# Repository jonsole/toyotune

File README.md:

# toyotune

Reverse engineering and ROM tuning for Toyota ECUs built on the Toshiba/Denso
8X (D8X) microcontroller — a proprietary part with an instruction set derived
from the Motorola 68HC11.

The best entry point is
**[Inside the 3S-GTE ECU](roms/3S-GTE/gen3/ecu_overview.md)**, an
architectural tour of the 1993 SW20 MR2 turbo ECU: three processors, adaptive
fuel trim and per-cylinder knock learning in 16 KB of ROM.

## What's here

- **[`roms/`](roms/)** — disassembly, annotation and tuned-ROM production.
  One directory per engine family (1G-GTE, 1G-GZE, 1JZ-GTE, 1UZ-FE, 3S-GE,
  3S-GTE, 3VZ-FE, 4A-GE), each holding one subdirectory per ECU part number.
  - [`roms/3S-GTE/`](roms/3S-GTE/) is the most thoroughly documented family —
    its [README](roms/3S-GTE/README.md) maps every part number to market,
    vehicle and CPU, and [`gen3/`](roms/3S-GTE/gen3/) holds the subsystem
    write-ups.
  - [`roms/docs/`](roms/docs/) documents the D8X MCU itself — instruction
    set, opcode matrix, registers — which every family here shares.
  - [`roms/d8x_assembler/`](roms/d8x_assembler/) is a Python reimplementation
    of the D8X assembler, and what the Makefiles actually build with.
- **[`hw/`](hw/)** — the Toyotune interface board: PCB, CPLD and host-MCU
  firmware for reading and rewriting these ECUs, including live access while
  the engine is running.
- **`sw/`** — IDA Pro installs used to open the `.idb` databases.

## Status

Ongoing and incomplete. The 3S-GTE Gen 3 pair is the furthest along; other
families are largely raw disassembly. Coverage is stated honestly in each
document — see
[session_journal.md](roms/3S-GTE/gen3/session_journal.md) for what is done
and what is pending.

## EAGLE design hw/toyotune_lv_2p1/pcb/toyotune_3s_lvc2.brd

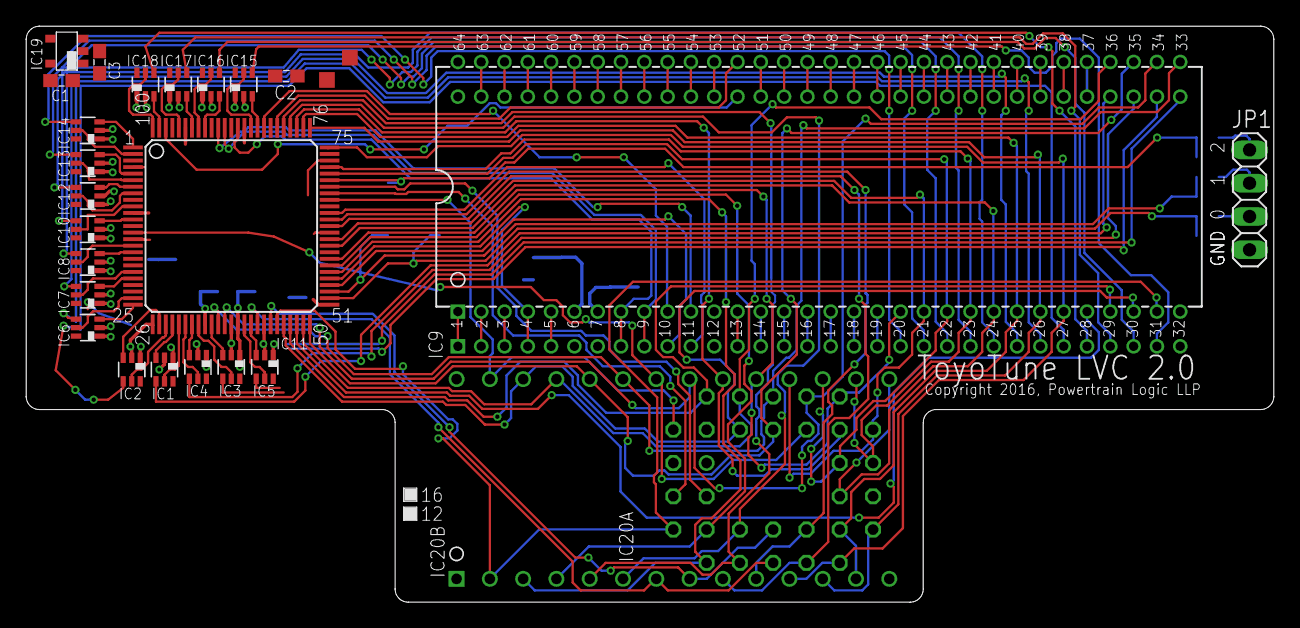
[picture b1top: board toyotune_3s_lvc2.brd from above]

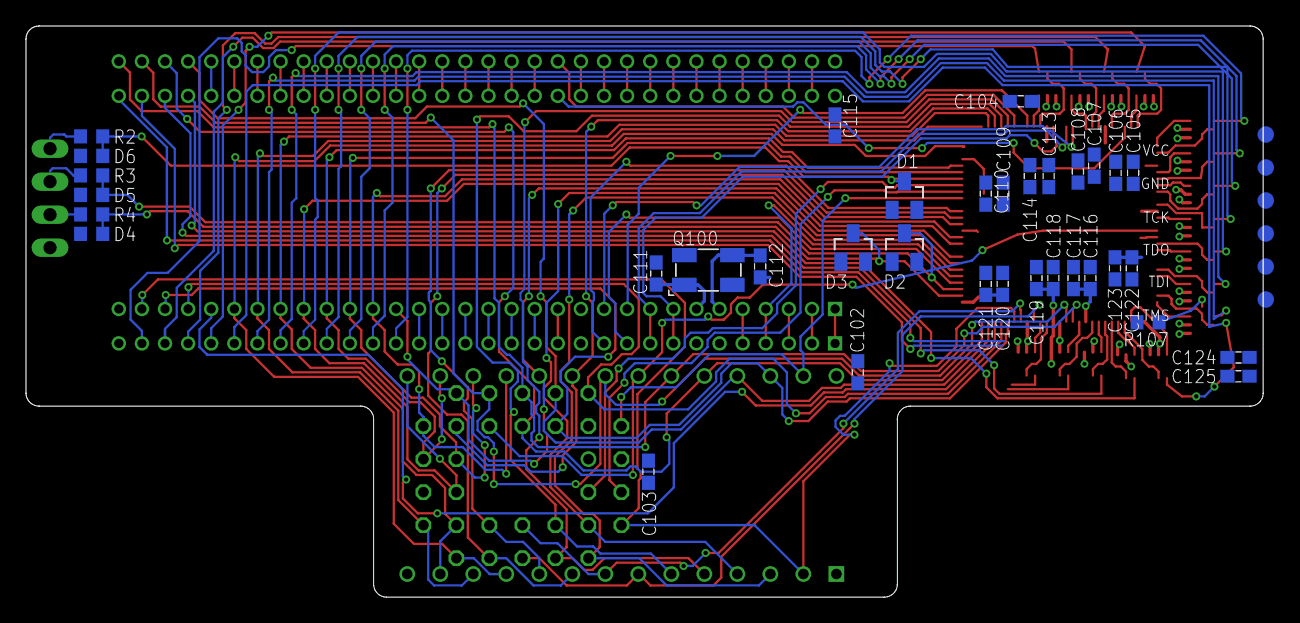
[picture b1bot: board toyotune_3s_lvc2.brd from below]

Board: 2 copper layers, 95.2 x 44.0 mm, 64 parts (36 on the bottom side), 138 nets.

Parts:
C1, C3: 1uF; C0603
C2, C102, C103, C104, C105, C107, C110, C114, C115, C116, C119, C120, C123, C124, C125: 0.1uF; C0603
C106, C108, C109, C113, C117, C118, C121, C122: 0.01uF; C0603
C111, C112: 10pF; C0603
D1, D2, D3: BAT54S; SOT23
D4, D5, D6: PGB1010603; R0603
IC1, IC2, IC3, IC4, IC5, IC6, IC7, IC8, IC10, IC12, IC13, IC15, IC16, IC17, IC18: SN74LVC1T45DCK; DCK_R-PDSO-G6
IC9: D15180X-XXXX; SDIP-64
IC11: XCR3128XL; VQ100
IC14: SN74LVC1T45; DCK_R-PDSO-G6
IC19: TLV70033; DDC_R-PDSO-G5
IC20A: SST39SF020WH; S32
IC20B: AT29C256; PDIP28
JP1: 1X04
JP100: JTAG; 1X06_SMD
Q100: 16Mhz; CRYSTAL-SMD-5X3
R2, R3, R4: 470R; R0603
R107: 10K; R0603
TP_GND: TPSQTP12SQ; TP12SQ
TP_VCC: TPSQTP12SQ; TP12SQ
U1: D151803-CONN; SDIP-64-CONN

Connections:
!D_HALT: IC9.51, U1.51
!D_INIT: IC9.52, IC11.81
!D_IRL: IC9.5, U1.5
!D_IRP: IC9.4, IC11.55, U1.4
!D_NMI: IC9.3, U1.3
!D_RD: IC9.10, IC11.83
!D_TEST: IC9.49, U1.49
!D_WDC: IC9.53, U1.53
!D_WI: IC9.50, U1.50
!D_WR: IC9.11, IC11.89
!E_INIT: IC11.98, U1.52
!E_IS: IC11.54, U1.10
!E_OS: IC11.65, U1.11
!M_RD: IC11.14, IC20A.24, IC20B.22
!M_ROM_CS: IC11.78, IC20A.22, IC20B.20
C_DRA0: IC1.5, IC11.30
C_DRA1: IC4.5, IC11.31
C_DRA2: IC3.5, IC11.33
C_DRA3: IC5.5, IC11.40
C_DRA4: IC11.85, IC15.5
C_DRA5: IC11.93, IC16.5
C_DRA6: IC11.96, IC17.5
C_DRA7: IC11.100, IC18.5
C_DRB0: IC2.5, IC11.28
C_DRB1: IC6.5, IC11.24
C_DRB2: IC7.5, IC11.20
C_DRB3: IC8.5, IC11.16
C_DRB4: IC10.5, IC11.10
C_DRB5: IC11.8, IC12.5
C_DRB6: IC11.6, IC13.5
C_DRB7: IC11.2, IC14.5
C_PA0: IC1.3, IC11.29
C_PA1: IC4.3, IC11.32
C_PA2: IC3.3, IC11.35
C_PA3: IC5.3, IC11.41
C_PA4: IC11.84, IC15.3
C_PA5: IC11.92, IC16.3
C_PA6: IC11.94, IC17.3
C_PA7: IC11.99, IC18.3
C_PB0: IC2.3, IC11.27
C_PB1: IC6.3, IC11.25
C_PB2: IC7.3, IC11.21
C_PB3: IC8.3, IC11.17
C_PB4: IC10.3, IC11.12
C_PB5: IC11.7, IC12.3
C_PB6: IC11.5, IC13.3
C_PB7: IC11.1, IC14.3
D1_XIN: C112.2, IC9.6, Q100.3
D1_XOUT: C111.1, IC9.7, Q100.1
D_A8: IC9.36, IC11.49, IC20A.27, IC20B.25
D_A9: IC9.35, IC11.50, IC20A.26, IC20B.24
D_A10: IC9.34, IC11.37, IC20A.23, IC20B.21
D_A11: IC9.33, IC11.36, IC20A.25, IC20B.23
D_A12: IC9.31, IC11.45, IC20A.4, IC20B.2
D_A13: IC9.30, IC11.46, IC20A.28, IC20B.26
D_A14: IC9.29, IC11.47, IC20A.29
D_A15: IC9.28, IC11.48
D_ADR: IC9.9, IC11.90, U1.9
D_AL0: IC11.64, IC20A.12, IC20B.10
D_AL1: IC11.63, IC20A.11, IC20B.9
D_AL2: IC11.44, IC20A.10, IC20B.8
D_AL3: IC11.42, IC20A.9, IC20B.7
D_AL4: IC11.79, IC20A.8, IC20B.6
D_AL5: IC11.80, IC20A.7, IC20B.5
D_AL6: IC11.57, IC20A.6, IC20B.4
D_AL7: IC11.56, IC20A.5, IC20B.3
D_ASR0: IC9.2, U1.2
D_ASR1: IC9.1, U1.1
D_ASR2: IC9.63, U1.63
D_ASR3: IC9.62, U1.62
D_CCLK: IC9.8, IC11.87, U1.8
D_DA0: IC9.27, IC11.75, IC20A.13, IC20B.11
D_DA1: IC9.26, IC11.76, IC20A.14, IC20B.12
D_DA2: IC9.25, IC11.77, IC20A.15, IC20B.13
D_DA3: IC9.24, IC11.60, IC20A.17, IC20B.15
D_DA4: IC9.23, IC11.72, IC20A.18, IC20B.16
D_DA5: IC9.22, IC11.71, IC20A.19, IC20B.17
D_DA6: IC9.21, IC11.61, IC20A.20, IC20B.18
D_DA7: IC9.20, IC11.58, IC20A.21, IC20B.19
D_DOUT0: IC9.61, U1.61
D_DOUT1: IC9.60, U1.60
D_DOUT2: IC9.59, U1.59
D_DOUT3: IC9.58, U1.58
D_DOUT4: IC9.57, U1.57
D_DOUT5: IC9.56, U1.56
D_DOUT6: IC9.55, U1.55
D_DOUT7: IC9.54, U1.54
D_PA0: IC1.4, U1.36
D_PA1: IC4.4, U1.35
D_PA2: IC3.4, U1.34
D_PA3: IC5.4, U1.33
D_PA4: IC15.4, U1.31
D_PA5: IC16.4, U1.30
D_PA6: IC17.4, U1.29
D_PA7: IC18.4, U1.28
D_PB0: IC2.4, U1.27
D_PB1: IC6.4, U1.26
D_PB2: IC7.4, U1.25
D_PB3: IC8.4, U1.24
D_PB4: IC10.4, U1.23
D_PB5: IC12.4, U1.22
D_PB6: IC13.4, U1.21
D_PB7: IC14.4, U1.20
D_PC0: IC9.48, U1.48
D_PC1: IC9.47, U1.47
D_PC2: IC9.46, U1.46
D_PC3: IC9.45, U1.45
D_PC4: IC9.44, U1.44
D_PC5: IC9.43, U1.43
D_PC6: IC9.42, U1.42
D_PC7: IC9.41, U1.41
D_PD0: IC9.40, U1.40
D_PD1: IC9.39, U1.39
D_PD2: IC9.38, U1.38
D_PD3: IC9.37, U1.37
D_SCLK: IC9.13, U1.13
D_SIN0: IC9.17, U1.17
D_SIN1: IC9.16, U1.16
D_SIN2: IC9.15, U1.15
D_SIN3: IC9.14, U1.14
D_SOUT0: IC9.19, U1.19
D_SOUT1: IC9.18, U1.18
GND: C1.2, C2.1, C3.2, C102.1, C103.1, C104.1, C105.1, C106.1, C107.1, C108.1, C109.1, C110.1, C111.2, C112.1, C113.1, C114.1, C115.1, C116.1, C117.1, C118.1, C119.1, C120.1, C121.1, C122.1, C123.1, C124.1, C125.1, D1.1, D2.1, D3.1, D4.1, D5.1, D6.1, IC1.2, IC2.2, IC3.2, IC4.2, IC5.2, IC6.2, IC7.2, IC8.2, IC9.12, IC9.32, IC10.2, IC11.11, IC11.26, IC11.38, IC11.43, IC11.59, IC11.74, IC11.86, IC11.95, IC12.2, IC13.2, IC14.2, IC15.2, IC16.2, IC17.2, IC18.2, IC19.2, IC20A.1, IC20A.16, IC20B.14, JP1.1, JP100.GND, TP_GND.TP, U1.32
MSEL0: D3.3, D4.2, IC11.52, R4.1
MSEL0_ECU: JP1.2, R4.2
MSEL1: D2.3, D5.2, IC11.53, R3.1
MSEL1_ECU: JP1.3, R3.2
MSEL2: D1.3, D6.2, IC11.70, R2.1
MSEL2_ECU: JP1.4, R2.2
M_A15: IC11.69, IC20A.3
M_A16: IC11.68, IC20A.2
M_A17/M_A14: IC11.67, IC20A.30, IC20B.27
TCK: IC11.62, JP100.TCK
TDI: IC11.4, JP100.TDI
TDO: IC11.73, JP100.TDO
TMS: IC11.15, JP100.TMS, R107.1
VCC: C2.2, C3.1, C102.2, C103.2, C115.2, C124.2, IC1.6, IC2.6, IC3.6, IC4.6, IC5.6, IC6.6, IC7.6, IC8.6, IC9.64, IC10.6, IC12.6, IC13.6, IC14.6, IC15.6, IC16.6, IC17.6, IC18.6, IC19.1, IC19.3, IC20A.31, IC20A.32, IC20B.1, IC20B.28, TP_VCC.TP, U1.64
VCC_CPLD: C1.1, C104.2, C105.2, C106.2, C107.2, C108.2, C109.2, C110.2, C113.2, C114.2, C116.2, C117.2, C118.2, C119.2, C120.2, C121.2, C122.2, C123.2, C125.2, D1.2, D2.2, D3.2, IC1.1, IC2.1, IC3.1, IC4.1, IC5.1, IC6.1, IC7.1, IC8.1, IC10.1, IC11.3, IC11.18, IC11.34, IC11.39, IC11.51, IC11.66, IC11.82, IC11.91, IC12.1, IC13.1, IC14.1, IC15.1, IC16.1, IC17.1, IC18.1, IC19.5, JP100.VCC, R107.2

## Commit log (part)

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2018-05-18 Initial commit with PCB schematics and CPLD VHDL.
2018-05-22 Set theme jekyll-theme-midnight
2018-09-20 Add IDA Free plugin for Denso 8X CPU
2018-09-20 Adding ROMs and tools.
2021-01-05 Set TASMTABS.
2021-01-05 Remove directory
2021-01-05 Add modified ST205 images back in
2026-04-23 Denso 8 docs
2026-04-24 Knock Sensor Details
2026-04-27 Add files via upload
    ADC details
2026-04-27 Add files via upload
    Knock detection details

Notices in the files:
hw/toyotune_lv_2p1/pcb/toyotune_3s_lvc2.brd:
Copyright 2016, Powertrain Logic LLP
